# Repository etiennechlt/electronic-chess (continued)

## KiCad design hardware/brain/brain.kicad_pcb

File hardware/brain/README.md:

# Cerveau : carte principale du plateau

Carte générée par `tools/boardgen` (module `brain`) depuis
`config/board.yaml` (ADR 0010). 120 x 80 mm, 4 couches : F.Cu
composants et signaux, In1 plan de masse, In2 alimentations et
signaux longs, B.Cu signaux. Elle vit au fond de la base, sur
l'empreinte commune aux deux bases.

## Blocs

- **MCU** : STM32G474RE soudé (LQFP-64), sans quartz (HSI plus CRS sur
  l'USB), boutons RESET et BOOT, connecteur SWD 2 x 5 au pas 1,27 mm
  (SWO et TDI laissés libres), USB-C en périphérique (USBLC6-2 en
  protection, 5,1 k sur CC, VBUS non utilisé : la carte se nourrit du
  pack). Le tableau des broches est `plateau.brain.mcu_pins` dans le
  yaml, relu contre la fiche technique dans la
  [note 14](../../docs/notes/14-revue-des-cartes.md) (quatre entrées ADC
  sur quatre convertisseurs distincts, PB8 sert de BOOT0, PG10 de NRST).
- **Liens quadrants** : quatre connecteurs FPC 16 broches (même
  brochage que le quadrant), bus d'adresses et d'enables partagé,
  quatre sorties analogiques vers quatre ADC à travers 49,9 ohms et
  1 nF, chaîne LED sérialisée d'un quadrant au suivant, tampon
  74AHCT1G125 à la source.
- **Alimentation** : fusible d'entrée, buck TPS62130 3 A à 2,5 MHz en
  PWM forcé (DEF haut) pour le 5 V, AP2112K pour le 3,3 V logique,
  LP2985 plus perle de ferrite pour l'îlot 5VA des quadrants, rail
  12 V d'impulsion (VIN) fusé avec sa réserve de 100 µF, rail LED fusé.
- **Communication** : UART tamponnée par un ADuM1201 (GND2 sur la masse
  commune : pas d'isolation galvanique tant que le module est sur la
  carte), TXD0 du module vers l'entrée VIA, sortie VOB vers RXD0, load
  switch P-FET sur le 5 V du module, régulateur AMS1117 pour
  l'ESP32-S3-WROOM-1, cavalier JP1 pour alimenter le côté module depuis
  l'ESP32 ou le Pi, embase Pi 2 x 4, embase de programmation ESP 1 x 6,
  boutons BOOT et EN. Le module est au bord est, son antenne dépasse de
  6 mm de la carte et sa zone de dégagement (la cour KiCad, 48 x 41 mm)
  occupe le coin sud-est : le quatrième trou de fixation est remonté à
  mi-hauteur du bord est.
- **Liens** : IDC 2 x 10 vers la carte moteurs (VBAT, STEP, DIR, EN,
  UART TMC, fins de course, servo, 5 V, 3,3 V), 2 x 4 vers la carte
  puissance (VBAT, I2C, état de charge, touche de réveil).
- **Interface** : buzzer 12 mm sur transistor, quatre LED d'état,
  bouton utilisateur, points de test.

## Hygiène de signal

Le plan de masse In1 est continu ; les sorties analogiques arrivent au
bord nord avec leur filtre RC juste devant le MCU ; le module radio est
au coin sud-est, le plus loin des connecteurs de quadrant ; le buck est
au coin nord-est avec sa boucle de commutation courte. Le routeur pousse
les longs signaux sur les couches internes (coût majoré sur F.Cu et
B.Cu) et ne perce jamais de via dans le trou d'une pastille traversante.
Point ouvert de la revue : le LP2985 de l'îlot 5VA (SOT-23-5) dissipe
0,5 W depuis VBAT pour les quatre frontaux, un boîtier à pad thermique
est proposé.

## Régénérer

```bash
PYTHONPATH=tools .venv/bin/python -m boardgen build brain --render docs/images/brain.png
```

Le contrôle d'isolement exact tourne à chaque build ; les nets que le
routeur n'a pas fermés sont listés et restent à finir dans pcbnew.

## Résultat du build

Généré par `python -m boardgen build brain` le 20/09/2026 :

| Composants | Segments | Vias | Raccords de la passe | Nets fermés | Nets ouverts | Défauts d'isolement |
|---|---|---|---|---|---|---|
| 113 | 1528 | 476 | 6 | 92 | 0 | 0 |

Ce qui a fermé la carte, dans l'ordre où il a fallu le trouver
([note 04](../../docs/notes/04-routeur-et-garanties.md)) :

- les éventails des quatre liens FPC dessinés à la main (voies de
  0,3 mm en escalier sur la face avant, un petit via au bout de chacune,
  les masses descendues au plan à leur moignon), la bande médiane
  descendue sous eux ;
- le bus des quadrants, les alimentations, VBAT, les quatre sorties
  analogiques et les deux lignes UART de l'isolateur routés en premier,
  quand la carte est vide ;
- le haul VBAT dessiné à la main sur la face arrière, du lien moteurs
  au fusible F1 par le bord sud puis une colonne à l'ouest du lien
  puissance ;
- chaque LED d'état placée à côté de sa résistance ;
- les masses descendues au plan avant les signaux, une garde de 0,1 mm
  autour des pastilles CMS ;
- le rip-up et reroutage des nets murés, puis la passe de finition
  partagée (six raccords).

DRC KiCad 7 (`tools/drc.py`, zones remplies) : 220 signalements, aucun élément non connecté, aucune erreur ; avertissements sans effet sur la fabrication : lib_footprint_issues 113, silk_overlap 52, via_dangling 27, silk_over_copper 23, silk_edge_clearance 3, track_dangling 2. Le contrôle d'isolement exact du générateur ne signale aucun défaut. Les vias d'éventail des boîtiers fins font 0,45 mm (perçage 0,2 mm), dans les capacités standard de JLCPCB.

## Fabrication

`brain-gerbers.zip` (quatre couches de cuivre, masques, sérigraphies,
pâte, contour, perçages PTH et NPTH, fiche de travail) et son
empreinte `brain-gerbers.sha256`, produits par
`/usr/bin/python3 tools/gerbers.py hardware/brain/brain.kicad_pcb` ;
`sha256sum -c brain-gerbers.sha256` dans ce dossier vérifie que
l'archive est celle de la carte commitée. Commande et options du
formulaire dans la [note 23](../../docs/notes/23-commande-jlcpcb.md) :
120 x 80 mm, 4 couches, ENIG (LQFP au pas de 0,5 mm, QFN, quatre FPC),
cuivre interne standard. La nomenclature d'assemblage (`jlc-bom.csv`,
`jlc-cpl.csv`) est complète en références, mais ses codes LCSC restent
à vérifier ligne par ligne avant tout ordre d'assemblage
([note 22](../../docs/notes/22-erreurs-de-conception.md), point 11).

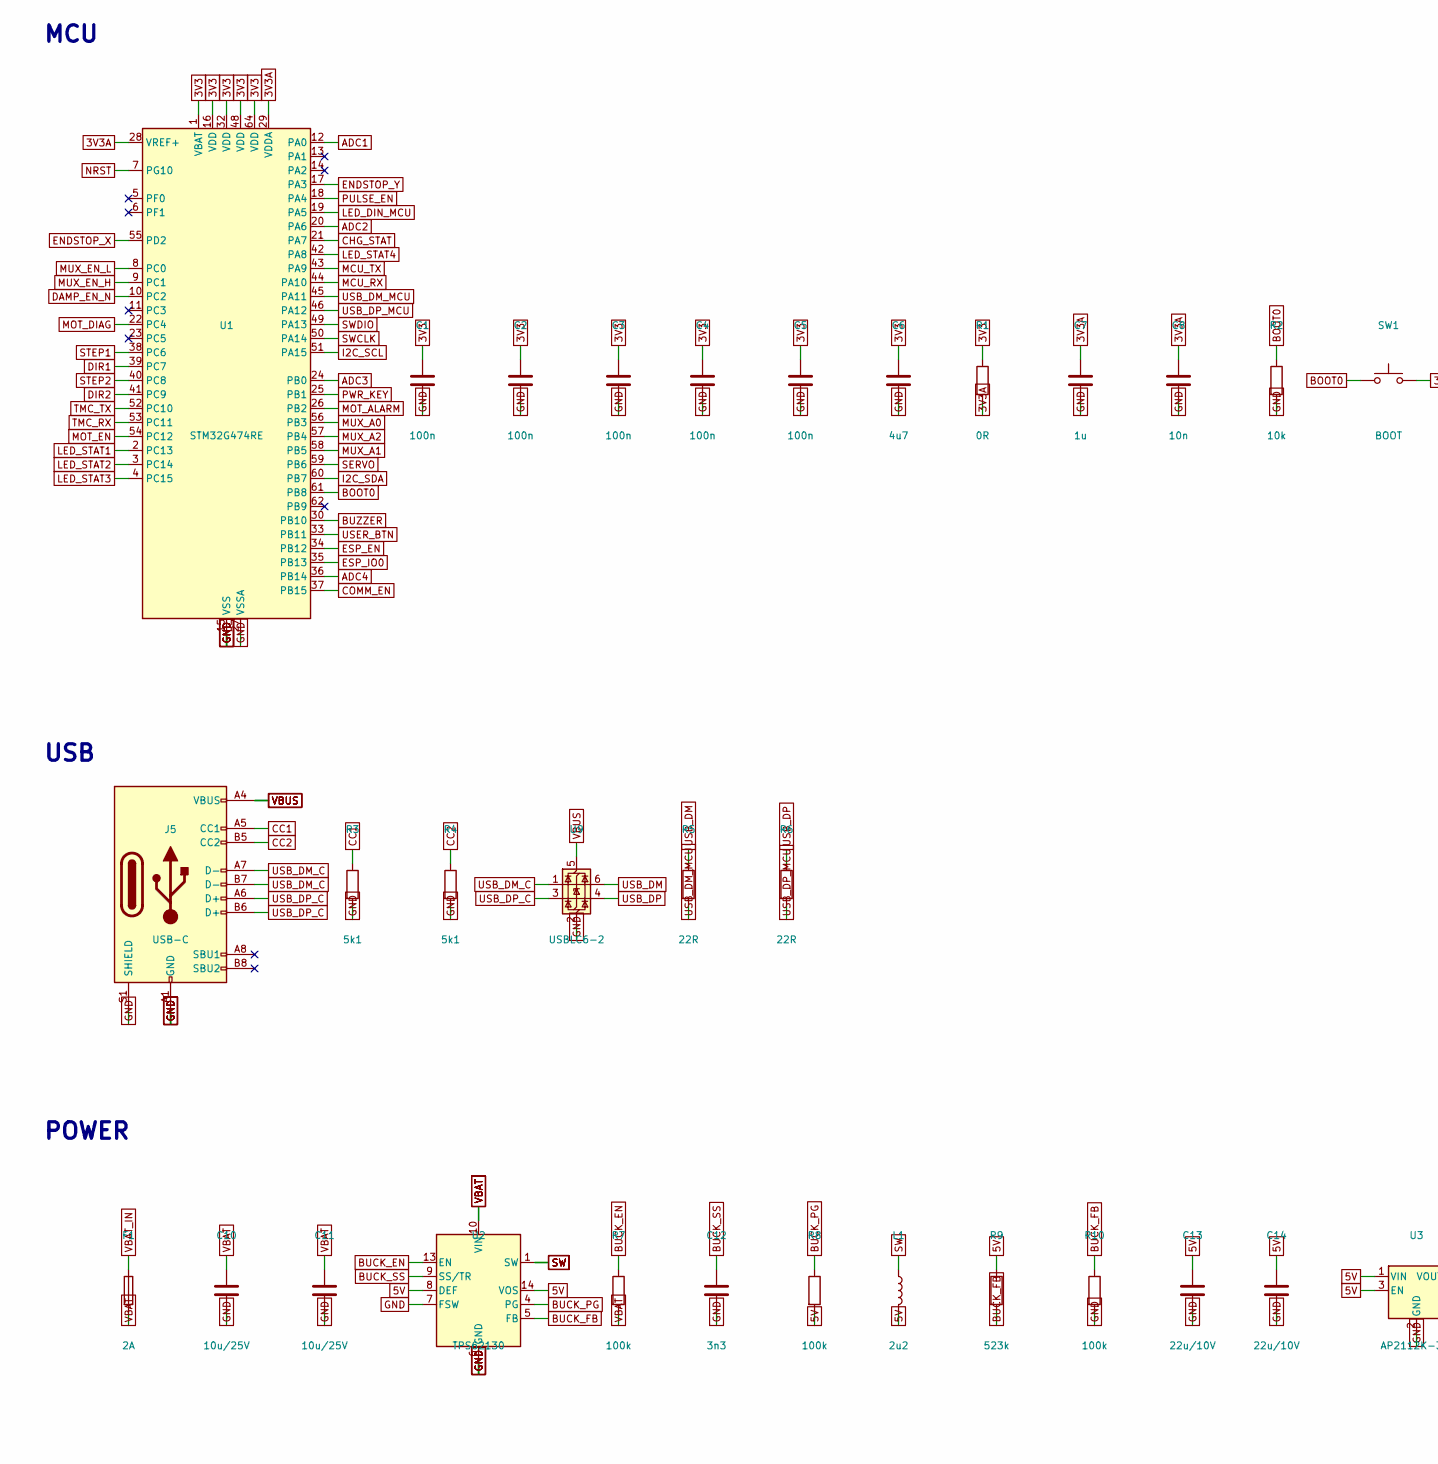
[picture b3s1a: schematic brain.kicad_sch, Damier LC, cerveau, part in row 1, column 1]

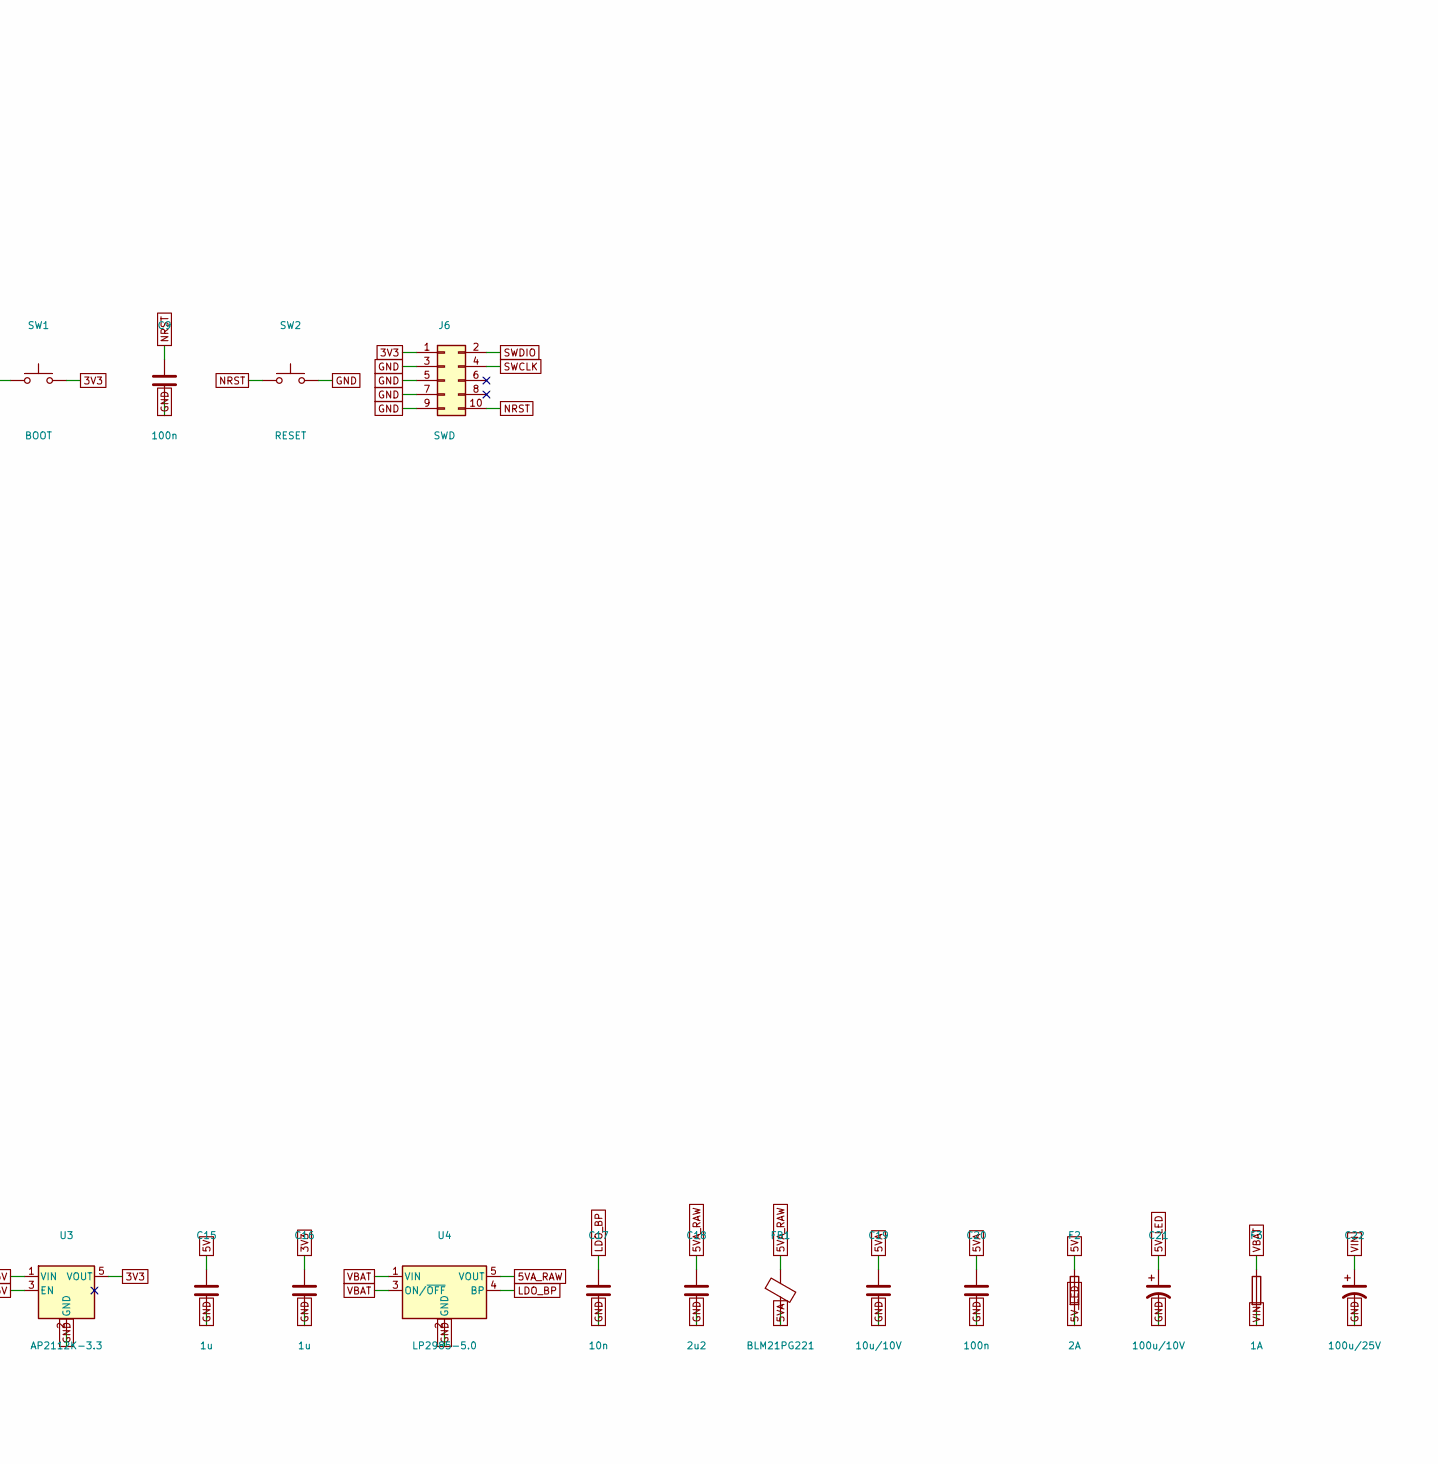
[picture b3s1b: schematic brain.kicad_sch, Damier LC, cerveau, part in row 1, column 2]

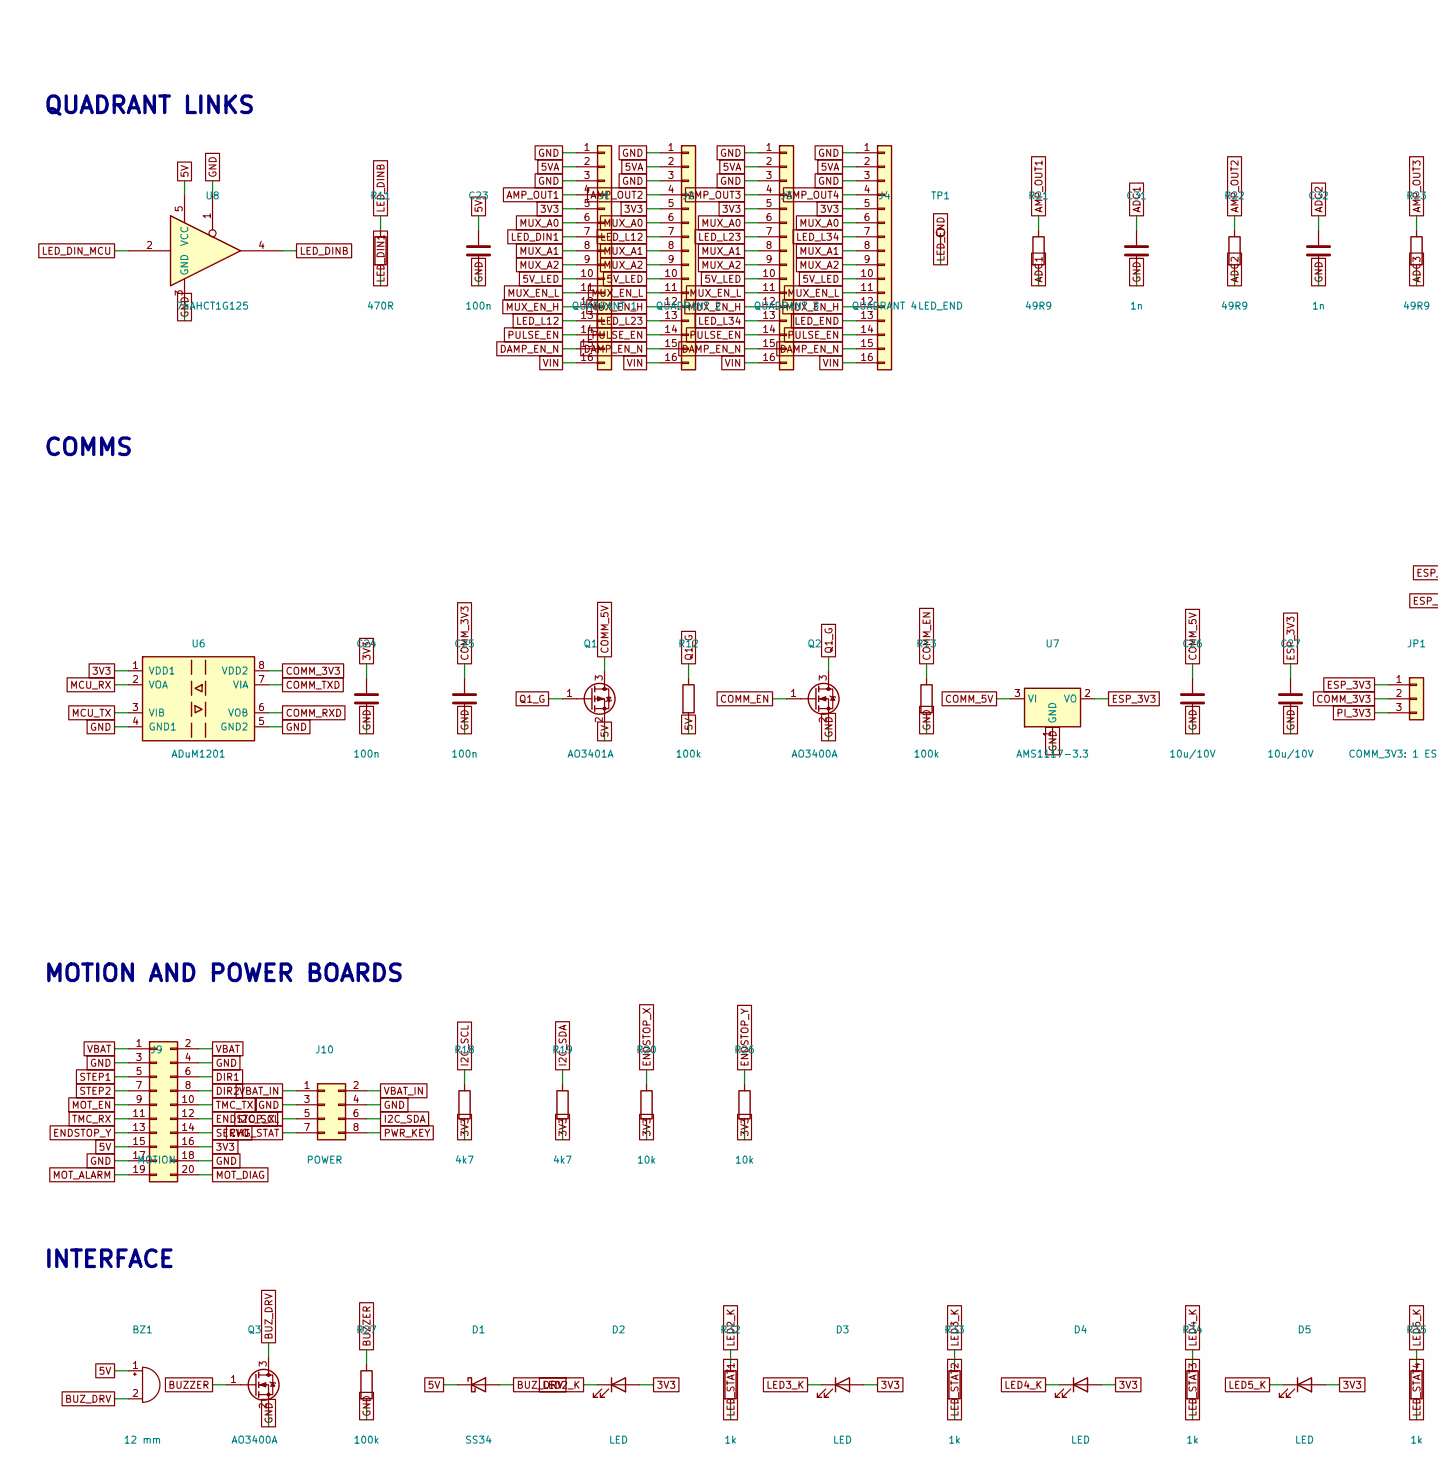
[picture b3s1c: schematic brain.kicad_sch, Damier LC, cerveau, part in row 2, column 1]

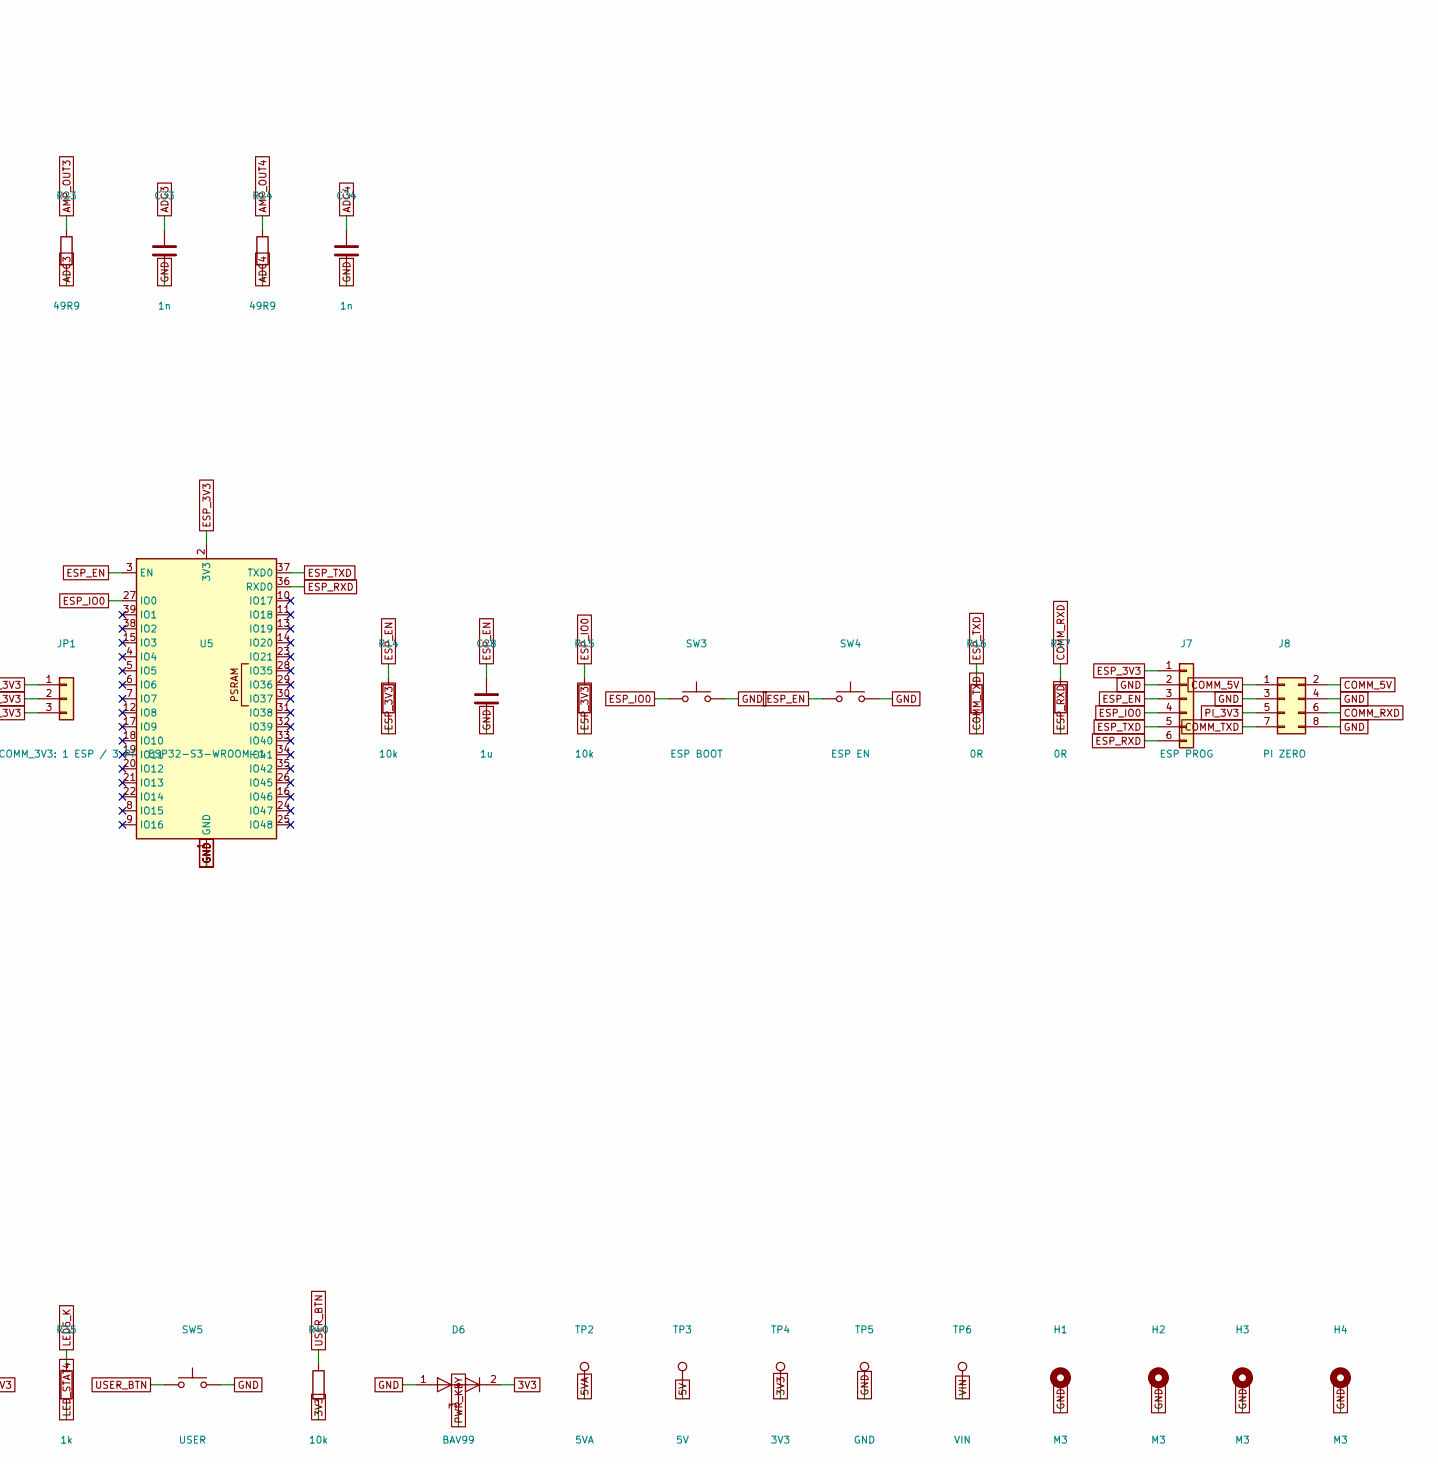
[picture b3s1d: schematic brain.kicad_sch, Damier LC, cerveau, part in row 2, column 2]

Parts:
BZ1: 12 mm; Buzzer_12x9.5RM7.6
C1, C2, C3, C4, C5, C9, C20, C23, C24, C25: 100n; C_0603_1608Metric
C6: 4u7; C_0603_1608Metric
C7, C15, C16, C28: 1u; C_0603_1608Metric
C8, C17: 10n; C_0603_1608Metric
C10, C11: 10u/25V; C_1206_3216Metric
C12: 3n3; C_0603_1608Metric
C13, C14: 22u/10V; C_1206_3216Metric
C18: 2u2; C_0603_1608Metric
C19, C26, C27: 10u/10V; C_1206_3216Metric
C21: 100u/10V; CP_Elec_6.3x7.7
C22: 100u/25V; CP_Elec_6.3x7.7
C31, C32, C33, C34: 1n; C_0603_1608Metric
D1: SS34; D_SMA; MPN SS34; LCSC C8678
D2, D3, D4, D5: LED; LED_0603_1608Metric; MPN 19-217/GHC-YR1S2/3T; LCSC C72043
D6: BAV99; SOT-23; MPN BAV99; LCSC C2500
F1, F2: 2A; Fuse_1206_3216Metric
F3: 1A; Fuse_1206_3216Metric
FB1: BLM21PG221; R_0805_2012Metric; MPN BLM21PG221SN1D; LCSC C18305
H1, H2, H3, H4: M3; MountingHole_3.2mm_M3_Pad
J1: QUADRANT 1; Hirose_FH12-16S-0.5SH_1x16-1MP_P0.50mm_Horizontal; MPN FH12-16S-0.5SH(55); LCSC C2837584
J2: QUADRANT 2; Hirose_FH12-16S-0.5SH_1x16-1MP_P0.50mm_Horizontal; MPN FH12-16S-0.5SH(55); LCSC C2837584
J3: QUADRANT 3; Hirose_FH12-16S-0.5SH_1x16-1MP_P0.50mm_Horizontal; MPN FH12-16S-0.5SH(55); LCSC C2837584
J4: QUADRANT 4; Hirose_FH12-16S-0.5SH_1x16-1MP_P0.50mm_Horizontal; MPN FH12-16S-0.5SH(55); LCSC C2837584
J5: USB-C; USB_C_Receptacle_GCT_USB4085; MPN USB4085-GF-A; LCSC C2988369
J6: SWD; PinHeader_2x05_P1.27mm_Vertical
J7: ESP PROG; PinHeader_1x06_P2.54mm_Vertical
J8: PI ZERO; PinHeader_2x04_P2.54mm_Vertical
J9: MOTION; PinHeader_2x10_P2.54mm_Vertical
J10: POWER; PinHeader_2x04_P2.54mm_Vertical
JP1: COMM_3V3: 1 ESP / 3 PI; PinHeader_1x03_P2.54mm_Vertical
L1: 2u2; L_Bourns_SRN6045TA; MPN SRN6045TA-2R2M; LCSC C167219
Q1: AO3401A; SOT-23; MPN AO3401A; LCSC C15127
Q2, Q3: AO3400A; SOT-23; MPN AO3400A; LCSC C20917
R1, R16, R17: 0R; R_0603_1608Metric
R2, R14, R15, R20, R26, R40: 10k; R_0603_1608Metric
R3, R4: 5k1; R_0603_1608Metric
R5, R6: 22R; R_0603_1608Metric
R7, R8, R10, R12, R13, R27: 100k; R_0603_1608Metric
R9: 523k; R_0603_1608Metric
R11: 470R; R_0603_1608Metric
R18, R19: 4k7; R_0603_1608Metric
R21, R22, R23, R24: 49R9; R_0603_1608Metric
R32, R33, R34, R35: 1k; R_0603_1608Metric
SW1: BOOT; SW_SPST_PTS645; MPN PTS645SM43SMTR92; LCSC C221929
SW2: RESET; SW_SPST_PTS645; MPN PTS645SM43SMTR92; LCSC C221929
SW3: ESP BOOT; SW_SPST_PTS645; MPN PTS645SM43SMTR92; LCSC C221929
SW4: ESP EN; SW_SPST_PTS645; MPN PTS645SM43SMTR92; LCSC C221929
SW5: USER; SW_SPST_PTS645; MPN PTS645SM43SMTR92; LCSC C221929
TP1: LED_END; TestPoint_Pad_1.5x1.5mm
TP2: 5VA; TestPoint_Pad_1.5x1.5mm
TP3: 5V; TestPoint_Pad_1.5x1.5mm
TP4: 3V3; TestPoint_Pad_1.5x1.5mm
TP5: GND; TestPoint_Pad_1.5x1.5mm
TP6: VIN; TestPoint_Pad_1.5x1.5mm
U1: STM32G474RE; LQFP-64_10x10mm_P0.5mm; MPN STM32G474RET6; LCSC C528140
U2: TPS62130; QFN-16-1EP_3x3mm_P0.5mm_EP1.75x1.75mm; MPN TPS62130RGTR; LCSC C74016
U3: AP2112K-3.3; SOT-23-5; MPN AP2112K-3.3TRG1; LCSC C51118
U4: LP2985-5.0; SOT-23-5; MPN LP2985AIM5-5.0; LCSC C129541
U5: ESP32-S3-WROOM-1; MPN ESP32-S3-WROOM-1-N8; LCSC C2913204
U6: ADuM1201; SOIC-8_3.9x4.9mm_P1.27mm; MPN ADuM1201ARZ; LCSC C123211
U7: AMS1117-3.3; SOT-223-3_TabPin2; MPN AMS1117-3.3; LCSC C6186
U8: 74AHCT1G125; SOT-23-5; MPN SN74AHCT1G125DBVR; LCSC C350557
U9: USBLC6-2; SOT-23-6; MPN USBLC6-2SC6; LCSC C7519

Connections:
3V3: C1.1, C2.1, C3.1, C4.1, C5.1, C6.1, C16.1, C24.1, D2.2 (A), D3.2 (A), D4.2 (A), D5.2 (A), D6.2 (A), J1.5, J2.5, J3.5, J4.5, J6.1, J9.16, R1.1, R18.2, R19.2, R20.2, R26.2, R40.2, SW1.2, TP4.1, U1.1 (VBAT), U1.16 (VDD), U1.32 (VDD), U1.48 (VDD), U1.64 (VDD), U3.5 (VOUT), U6.1 (VDD1)
3V3A: C7.1, C8.1, R1.2, U1.28 (VREF+), U1.29 (VDDA)
5V: BZ1.1 (+), C13.1, C14.1, C15.1, C23.1, D1.1 (K), F2.1, J9.15, L1.2, Q1.2 (S), R8.2, R9.1, R12.2, TP3.1, U2.8 (DEF), U2.14 (VOS), U3.1 (VIN), U3.3 (EN), U8.5 (VCC)
5VA: C19.1, C20.1, FB1.2, J1.2, J2.2, J3.2, J4.2, TP2.1
5VA_RAW: C18.1, FB1.1, U4.5 (VOUT)
5V_LED: C21.1, F2.2, J1.10, J2.10, J3.10, J4.10
ADC1: C31.1, R21.2, U1.12 (PA0)
ADC2: C32.1, R22.2, U1.20 (PA6)
ADC3: C33.1, R23.2, U1.24 (PB0)
ADC4: C34.1, R24.2, U1.36 (PB14)
AMP_OUT1: J1.4, R21.1
AMP_OUT2: J2.4, R22.1
AMP_OUT3: J3.4, R23.1
AMP_OUT4: J4.4, R24.1
BOOT0: R2.1, SW1.1, U1.61 (PB8)
BUCK_EN: R7.1, U2.13 (EN)
BUCK_FB: R9.2, R10.1, U2.5 (FB)
BUCK_PG: R8.1, U2.4 (PG)
BUCK_SS: C12.1, U2.9 (SS/TR)
BUZZER: Q3.1 (G), R27.1, U1.30 (PB10)
BUZ_DRV: BZ1.2 (-), D1.2 (A), Q3.3 (D)
CC1: J5.A5 (CC1), R3.1
CC2: J5.B5 (CC2), R4.1
CHG_STAT: J10.7, U1.21 (PA7)
COMM_3V3: C25.1, JP1.2, U6.8 (VDD2)
COMM_5V: C26.1, J8.1, J8.2, Q1.3 (D), U7.3 (VI)
COMM_EN: Q2.1 (G), R13.1, U1.37 (PB15)
COMM_RXD: J8.6, R17.1, U6.6 (VOB)
COMM_TXD: J8.7, R16.2, U6.7 (VIA)
DAMP_EN_N: J1.15, J2.15, J3.15, J4.15, U1.10 (PC2)
DIR1: J9.6, U1.39 (PC7)
DIR2: J9.8, U1.41 (PC9)
ENDSTOP_X: J9.12, R20.1, U1.55 (PD2)
ENDSTOP_Y: J9.13, R26.1, U1.17 (PA3)
ESP_3V3: C27.1, J7.1, JP1.1, R14.2, R15.2, U5.2 (3V3), U7.2 (VO)
ESP_EN: C28.1, J7.3, R14.1, SW4.1, U1.34 (PB12), U5.3 (EN)
ESP_IO0: J7.4, R15.1, SW3.1, U1.35 (PB13), U5.27 (IO0)
ESP_RXD: J7.6, R17.2, U5.36 (RXD0)
ESP_TXD: J7.5, R16.1, U5.37 (TXD0)
GND: C1.2, C2.2, C3.2, C4.2, C5.2, C6.2, C7.2, C8.2, C9.2, C10.2, C11.2, C12.2, C13.2, C14.2, C15.2, C16.2, C17.2, C18.2, C19.2, C20.2, C21.2, C22.2, C23.2, C24.2, C25.2, C26.2, C27.2, C28.2, C31.2, C32.2, C33.2, C34.2, D6.1 (K), H1.1, H2.1, H3.1, H4.1, J1.1, J1.3, J2.1, J2.3, J3.1, J3.3, J4.1, J4.3, J5.A1 (GND), J5.A12 (GND), J5.B1 (GND), J5.B12 (GND), J5.S1 (SHIELD), J6.3, J6.5, J6.7, J6.9, J7.2, J8.3, J8.4, J8.8, J9.3, J9.4, J9.17, J9.18, J10.3, J10.4, Q2.2 (S), Q3.2 (S), R2.2, R3.2, R4.2, R10.2, R13.2, R27.2, SW2.2, SW3.2, SW4.2, SW5.2, TP5.1, U1.15 (VSS), U1.27 (VSSA), U1.31 (VSS), U1.47 (VSS), U1.63 (VSS), U2.6 (GND), U2.7 (FSW), U2.15 (GND), U2.16 (GND), U2.17 (GND), U3.2 (GND), U4.2 (GND), U5.1 (GND), U5.40 (GND), U5.41 (GND), U6.4 (GND1), U6.5 (GND2), U7.1 (GND), U8.1, U8.3 (GND), U9.2 (GND)
I2C_SCL: J10.5, R18.1, U1.51 (PA15)
I2C_SDA: J10.6, R19.1, U1.60 (PB7)
LDO_BP: C17.1, U4.4 (BP)
LED2_K: D2.1 (K), R32.1
LED3_K: D3.1 (K), R33.1
LED4_K: D4.1 (K), R34.1
LED5_K: D5.1 (K), R35.1
LED_DIN1: J1.7, R11.2
LED_DINB: R11.1, U8.4
LED_DIN_MCU: U1.19 (PA5), U8.2
LED_END: J4.13, TP1.1
LED_L12: J1.13, J2.7
LED_L23: J2.13, J3.7
LED_L34: J3.13, J4.7
LED_STAT1: R32.2, U1.2 (PC13)
LED_STAT2: R33.2, U1.3 (PC14)
LED_STAT3: R34.2, U1.4 (PC15)
LED_STAT4: R35.2, U1.42 (PA8)
MCU_RX: U1.44 (PA10), U6.2 (VOA)
MCU_TX: U1.43 (PA9), U6.3 (VIB)
MOT_ALARM: J9.19, U1.26 (PB2)
MOT_DIAG: J9.20, U1.22 (PC4)
MOT_EN: J9.9, U1.54 (PC12)
MUX_A0: J1.6, J2.6, J3.6, J4.6, U1.56 (PB3)
MUX_A1: J1.8, J2.8, J3.8, J4.8, U1.58 (PB5)
MUX_A2: J1.9, J2.9, J3.9, J4.9, U1.57 (PB4)
MUX_EN_H: J1.12, J2.12, J3.12, J4.12, U1.9 (PC1)
MUX_EN_L: J1.11, J2.11, J3.11, J4.11, U1.8 (PC0)
NRST: C9.1, J6.10, SW2.1, U1.7 (PG10)
PI_3V3: J8.5, JP1.3
PULSE_EN: J1.14, J2.14, J3.14, J4.14, U1.18 (PA4)
PWR_KEY: D6.3 (K), J10.8, U1.25 (PB1)
Q1_G: Q1.1 (G), Q2.3 (D), R12.1
SERVO: J9.14, U1.59 (PB6)
STEP1: J9.5, U1.38 (PC6)
STEP2: J9.7, U1.40 (PC8)
SW: L1.1, U2.1 (SW), U2.2 (SW), U2.3 (SW)
SWCLK: J6.4, U1.50 (PA14)
SWDIO: J6.2, U1.49 (PA13)
TMC_RX: J9.11, U1.53 (PC11)
TMC_TX: J9.10, U1.52 (PC10)
USB_DM: R5.1, U9.6 (I/O1)
USB_DM_C: J5.A7 (D-), J5.B7 (D-), U9.1 (I/O1)
USB_DM_MCU: R5.2, U1.45 (PA11)
USB_DP: R6.1, U9.4 (I/O2)
USB_DP_C: J5.A6 (D+), J5.B6 (D+), U9.3 (I/O2)
USB_DP_MCU: R6.2, U1.46 (PA12)
USER_BTN: R40.1, SW5.1, U1.33 (PB11)
VBAT: C10.1, C11.1, F1.2, F3.1, J9.1, J9.2, R7.2, U2.10 (VIN), U2.11 (VIN), U2.12 (VIN), U4.1 (VIN), U4.3 (ON/~OFF)
VBAT_IN: F1.1, J10.1, J10.2
VBUS: J5.A4 (VBUS), J5.A9 (VBUS), J5.B4 (VBUS), J5.B9 (VBUS), U9.5 (VBUS)
VIN: C22.1, F3.2, J1.16, J2.16, J3.16, J4.16, TP6.1

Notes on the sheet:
MCU
USB
POWER
QUADRANT LINKS
COMMS
MOTION AND POWER BOARDS
INTERFACE

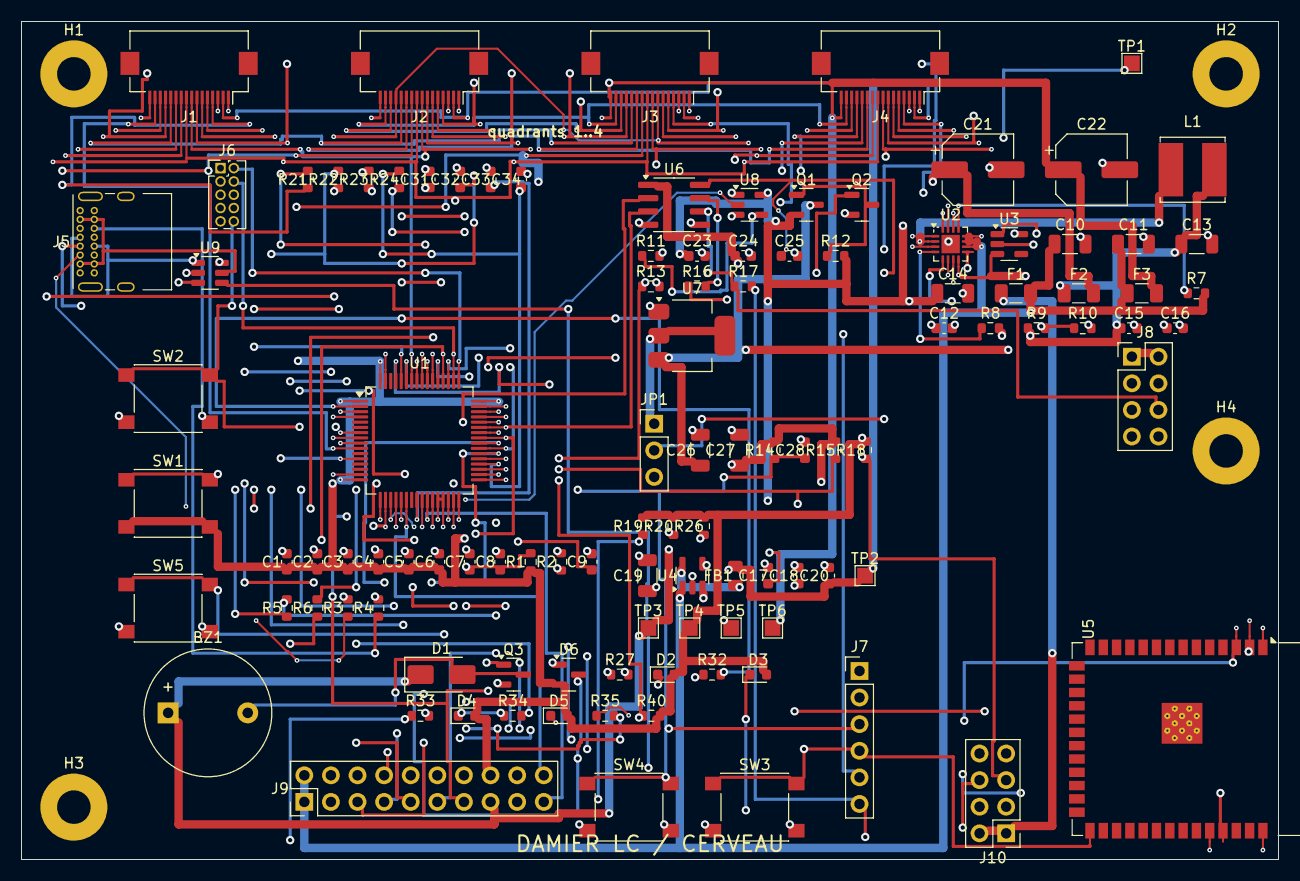
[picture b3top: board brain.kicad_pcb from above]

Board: 4 copper layers, 120.0 x 80.0 mm, 113 parts (0 on the bottom side), 92 nets.

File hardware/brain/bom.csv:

References,Qty,Value,Footprint,MPN,LCSC,DNP
BZ1,1,12 mm,Buzzer_12x9.5RM7.6,,,
C1 C2 C20 C23 C24 C25 C3 C4 C5 C9,10,100n,C_0603_1608Metric,,,
C10 C11,2,10u/25V,C_1206_3216Metric,,,
C12,1,3n3,C_0603_1608Metric,,,
C13 C14,2,22u/10V,C_1206_3216Metric,,,
C18,1,2u2,C_0603_1608Metric,,,
C19 C26 C27,3,10u/10V,C_1206_3216Metric,,,
C21,1,100u/10V,CP_Elec_6.3x7.7,,,
C22,1,100u/25V,CP_Elec_6.3x7.7,,,
C31 C32 C33 C34,4,1n,C_0603_1608Metric,,,
C6,1,4u7,C_0603_1608Metric,,,
C15 C16 C28 C7,4,1u,C_0603_1608Metric,,,
C17 C8,2,10n,C_0603_1608Metric,,,
D1,1,SS34,D_SMA,SS34,C8678,
D2 D3 D4 D5,4,LED,LED_0603_1608Metric,19-217/GHC-YR1S2/3T,C72043,
D6,1,BAV99,SOT-23,BAV99,C2500,
F1 F2,2,2A,Fuse_1206_3216Metric,,,
F3,1,1A,Fuse_1206_3216Metric,,,
FB1,1,BLM21PG221,R_0805_2012Metric,BLM21PG221SN1D,C18305,
H1 H2 H3 H4,4,M3,MountingHole_3.2mm_M3_Pad,,,
J1,1,QUADRANT 1,Hirose_FH12-16S-0.5SH_1x16-1MP_P0.50mm_Horizontal,FH12-16S-0.5SH(55),C2837584,
J10,1,POWER,PinHeader_2x04_P2.54mm_Vertical,,,
J2,1,QUADRANT 2,Hirose_FH12-16S-0.5SH_1x16-1MP_P0.50mm_Horizontal,FH12-16S-0.5SH(55),C2837584,
J3,1,QUADRANT 3,Hirose_FH12-16S-0.5SH_1x16-1MP_P0.50mm_Horizontal,FH12-16S-0.5SH(55),C2837584,
J4,1,QUADRANT 4,Hirose_FH12-16S-0.5SH_1x16-1MP_P0.50mm_Horizontal,FH12-16S-0.5SH(55),C2837584,
J5,1,USB-C,USB_C_Receptacle_GCT_USB4085,USB4085-GF-A,C2988369,
J6,1,SWD,PinHeader_2x05_P1.27mm_Vertical,,,
J7,1,ESP PROG,PinHeader_1x06_P2.54mm_Vertical,,,
J8,1,PI ZERO,PinHeader_2x04_P2.54mm_Vertical,,,
J9,1,MOTION,PinHeader_2x10_P2.54mm_Vertical,,,
JP1,1,COMM_3V3: 1 ESP / 3 PI,PinHeader_1x03_P2.54mm_Vertical,,,
L1,1,2u2,L_Bourns_SRN6045TA,SRN6045TA-2R2M,C167219,
Q1,1,AO3401A,SOT-23,AO3401A,C15127,
Q2 Q3,2,AO3400A,SOT-23,AO3400A,C20917,
R1 R16 R17,3,0R,R_0603_1608Metric,,,
R11,1,470R,R_0603_1608Metric,,,
R18 R19,2,4k7,R_0603_1608Metric,,,
R14 R15 R2 R20 R26 R40,6,10k,R_0603_1608Metric,,,
R21 R22 R23 R24,4,49R9,R_0603_1608Metric,,,
R3 R4,2,5k1,R_0603_1608Metric,,,
R32 R33 R34 R35,4,1k,R_0603_1608Metric,,,
R5 R6,2,22R,R_0603_1608Metric,,,
R10 R12 R13 R27 R7 R8,6,100k,R_0603_1608Metric,,,
R9,1,523k,R_0603_1608Metric,,,
SW1,1,BOOT,SW_SPST_PTS645,PTS645SM43SMTR92,C221929,
SW2,1,RESET,SW_SPST_PTS645,PTS645SM43SMTR92,C221929,
SW3,1,ESP BOOT,SW_SPST_PTS645,PTS645SM43SMTR92,C221929,
SW4,1,ESP EN,SW_SPST_PTS645,PTS645SM43SMTR92,C221929,
SW5,1,USER,SW_SPST_PTS645,PTS645SM43SMTR92,C221929,
TP1,1,LED_END,TestPoint_Pad_1.5x1.5mm,,,
TP2,1,5VA,TestPoint_Pad_1.5x1.5mm,,,
TP3,1,5V,TestPoint_Pad_1.5x1.5mm,,,
TP4,1,3V3,TestPoint_Pad_1.5x1.5mm,,,
TP5,1,GND,TestPoint_Pad_1.5x1.5mm,,,
TP6,1,VIN,TestPoint_Pad_1.5x1.5mm,,,
U1,1,STM32G474RE,LQFP-64_10x10mm_P0.5mm,STM32G474RET6,C528140,
U2,1,TPS62130,QFN-16-1EP_3x3mm_P0.5mm_EP1.75x1.75mm,TPS62130RGTR,C74016,
U3,1,AP2112K-3.3,SOT-23-5,AP2112K-3.3TRG1,C51118,
U4,1,LP2985-5.0,SOT-23-5,LP2985AIM5-5.0,C129541,
U5,1,ESP32-S3-WROOM-1,ESP32-S3-WROOM-1,ESP32-S3-WROOM-1-N8,C2913204,
U6,1,ADuM1201,SOIC-8_3.9x4.9mm_P1.27mm,ADuM1201ARZ,C123211,
U7,1,AMS1117-3.3,SOT-223-3_TabPin2,AMS1117-3.3,C6186,
U8,1,74AHCT1G125,SOT-23-5,SN74AHCT1G125DBVR,C350557,
U9,1,USBLC6-2,SOT-23-6,USBLC6-2SC6,C7519,
